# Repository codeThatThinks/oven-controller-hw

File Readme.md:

# MLL Electronics Oven Controller v1.0

A Raspberry Pi Zero-powered PID reflow oven controller -- PCB design files.

## Controller PCBA

## Display PCBA

## License

This project is licensed under the CERN-OHL-W v2. See LICENSE for more details.

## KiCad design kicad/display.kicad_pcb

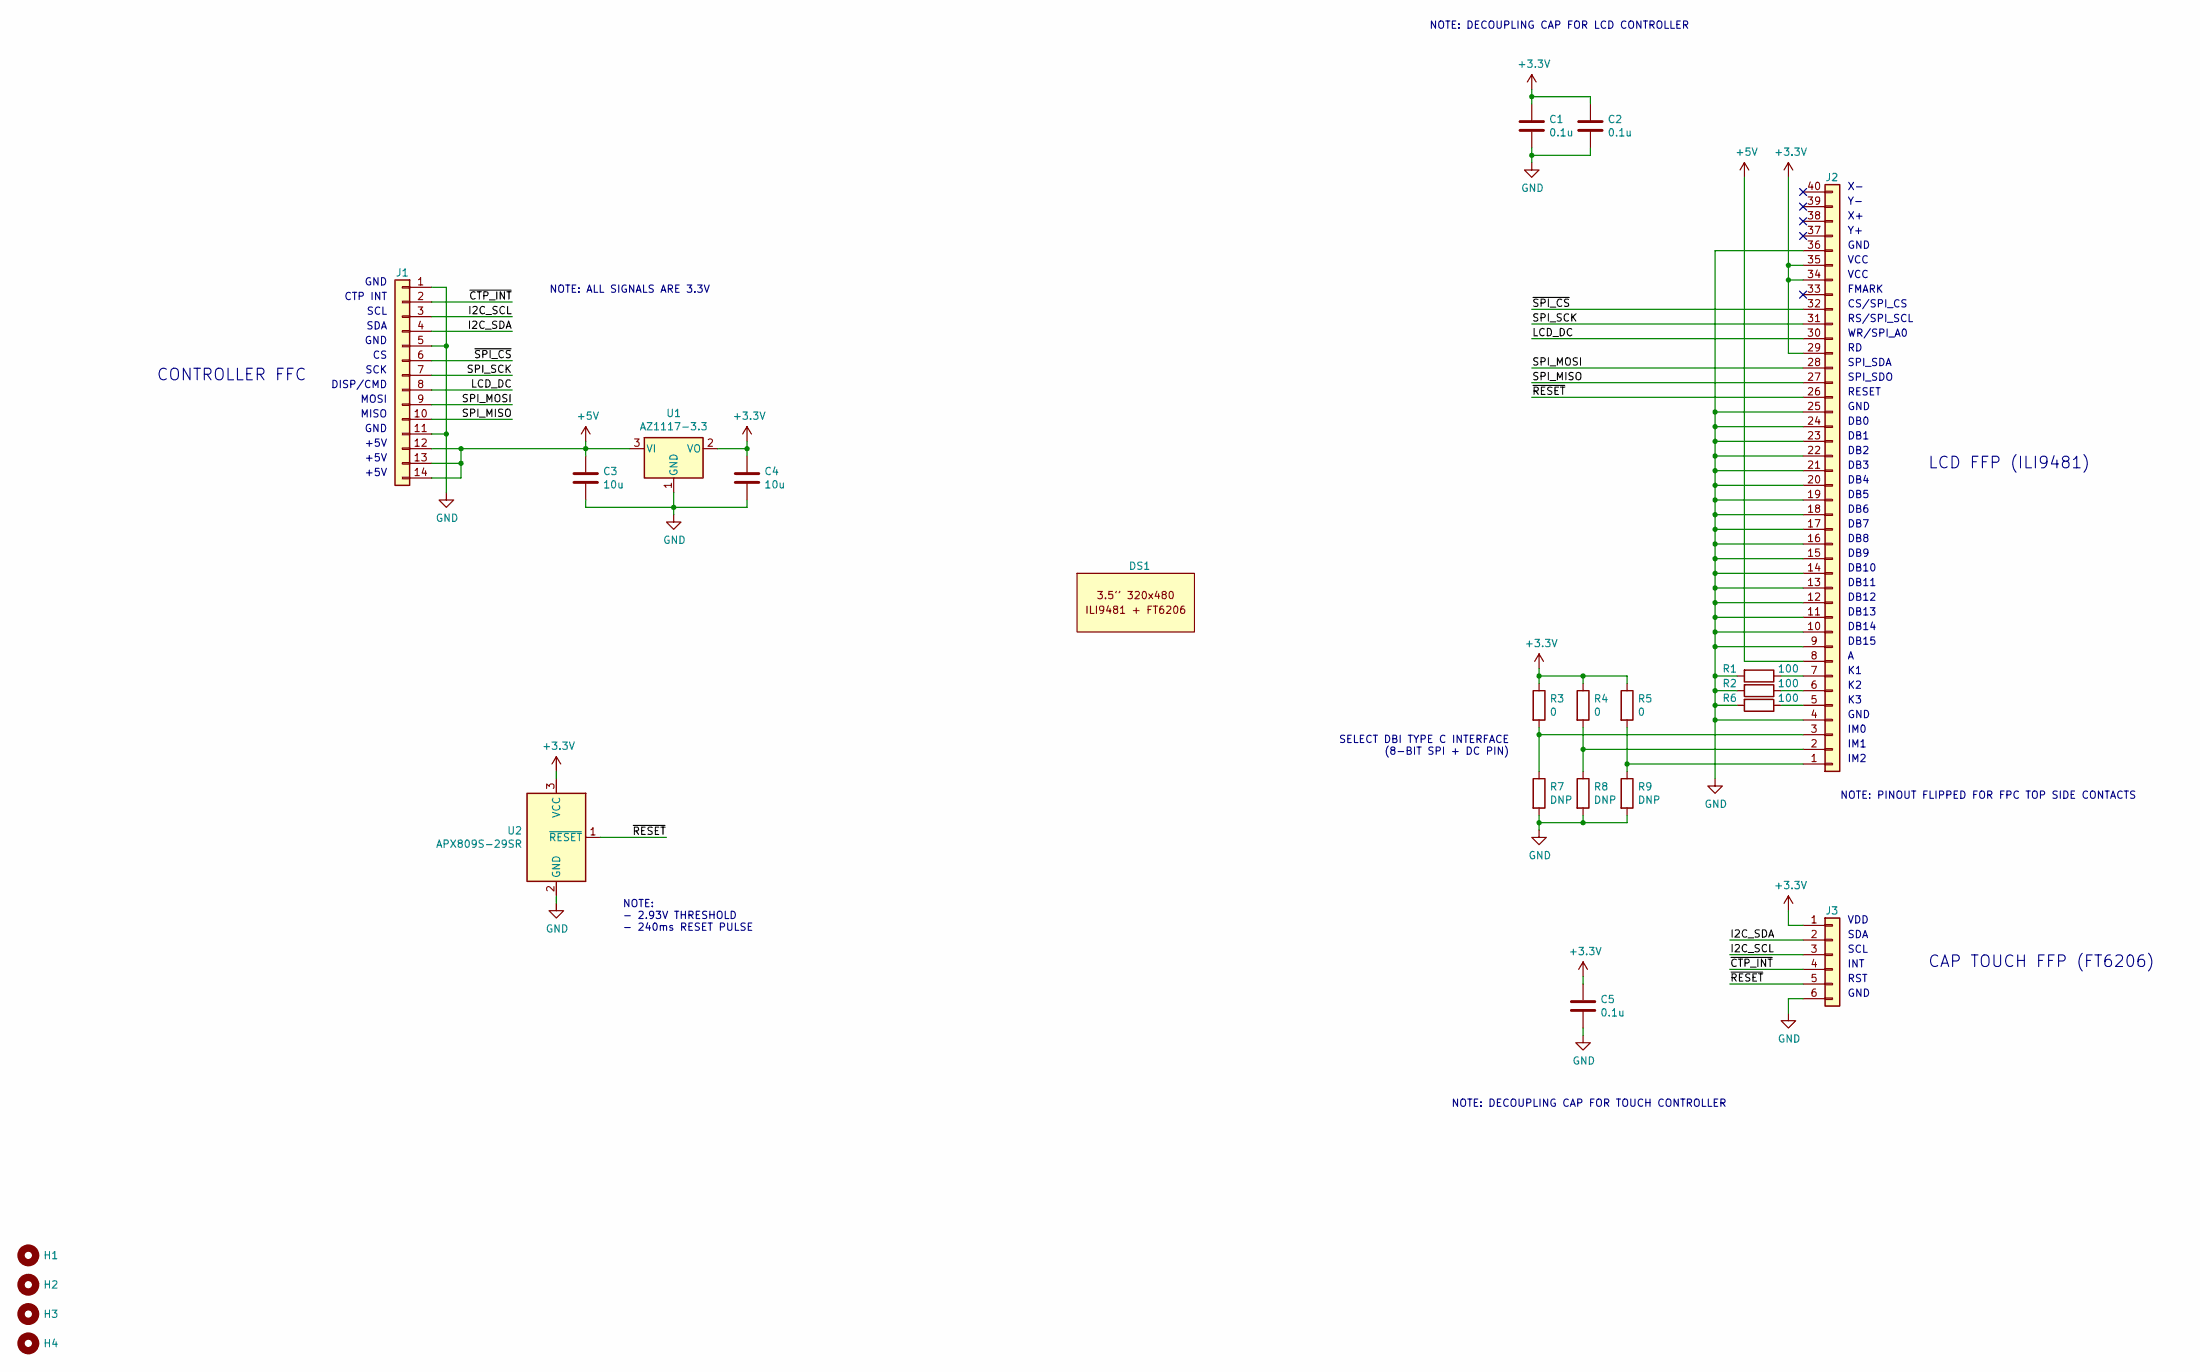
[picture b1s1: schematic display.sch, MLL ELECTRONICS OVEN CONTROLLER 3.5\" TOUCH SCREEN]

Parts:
C1, C2, C5: 0.1u; C_0603_1608Metric
C3, C4: 10u; C_0805_2012Metric
DS1: Display_LiangHaoCai_3.5in_IPS_CTP
H1, H2, H3, H4: MountingHole; MountingHole_3.2mm_M3
J1: CONTROLLER; TE_1-84953-4_1x14_1MP_P1.0_Horizontal
J2: LCD; GCT_FFC2B28-40-G_1x40_1MP_P0.50mm_Horizontal
J3: CTP; GCT_FFC2B28-06-G_1x6_1MP_P0.50mm_Horizontal
R1, R2, R6: 100; R_0603_1608Metric
R3, R4, R5: 0; R_0603_1608Metric
R7, R8, R9: DNP; R_0603_1608Metric
U1: AZ1117-3.3; SOT-223-3_TabPin2
U2: APX809S-29SR; SOT-23

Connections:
+3V3: C1.1, C2.1, C4.1, C5.1, J2.29, J2.34, J2.35, J3.1, R3.1, R4.1, R5.1, U1.2 (VO), U2.3 (VCC)
+5V: C3.1, J1.12, J1.13, J1.14, J2.8, U1.3 (VI)
/I2C_SCL: J1.3, J3.3
/I2C_SDA: J1.4, J3.2
/LCD_DC: J1.8, J2.30
/SPI_MISO: J1.10, J2.27
/SPI_MOSI: J1.9, J2.28
/SPI_SCK: J1.7, J2.31
/~CTP_INT: J1.2, J3.4
/~RESET: J2.26, J3.5, U2.1 (~RESET)
/~SPI_CS: J1.6, J2.32
GND: C1.2, C2.2, C3.2, C4.2, C5.2, J1.1, J1.5, J1.11, J2.4, J2.9, J2.10, J2.11, J2.12, J2.13, J2.14, J2.15, J2.16, J2.17, J2.18, J2.19, J2.20, J2.21, J2.22, J2.23, J2.24, J2.25, J2.36, J3.6, R1.2, R2.2, R6.2, R7.2, R8.2, R9.2, U1.1 (GND), U2.2 (GND)
unnamed: J2.1, R5.2, R9.1
unnamed: J2.2, R4.2, R8.1
unnamed: J2.3, R3.2, R7.1
unnamed: J2.5, R6.1
unnamed: J2.6, R2.1
unnamed: J2.7, R1.1

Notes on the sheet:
GND
VCC
FMARK
CS/SPI_CS
RS/SPI_SCL
WR/SPI_A0
SPI_SDA
SPI_SDO
RESET
DB0
DB1
DB2
DB3
DB4
DB5
DB6
DB7
DB8
DB9
DB10
DB11
DB12
DB13
DB14
DB15
IM0
IM1
IM2
LCD FFP (ILI9481)
CAP TOUCH FFP (FT6206)
VDD
SDA
SCL
INT
RST
NOTE: DECOUPLING CAP FOR LCD CONTROLLER
NOTE: DECOUPLING CAP FOR TOUCH CONTROLLER
NOTE: - 2.93V THRESHOLD - 240ms RESET PULSE
SCK
MOSI

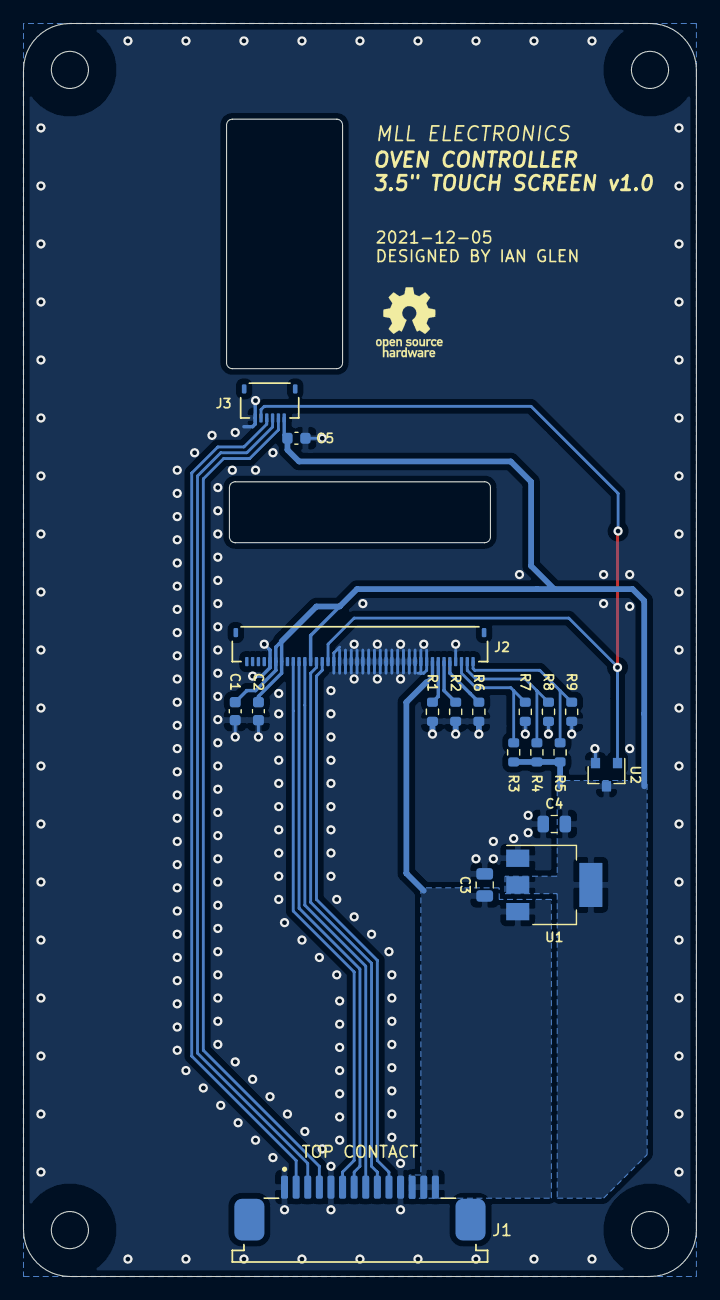
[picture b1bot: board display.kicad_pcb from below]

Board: 2 copper layers, 58.0 x 108.0 mm, 24 parts (19 on the bottom side), 18 nets.

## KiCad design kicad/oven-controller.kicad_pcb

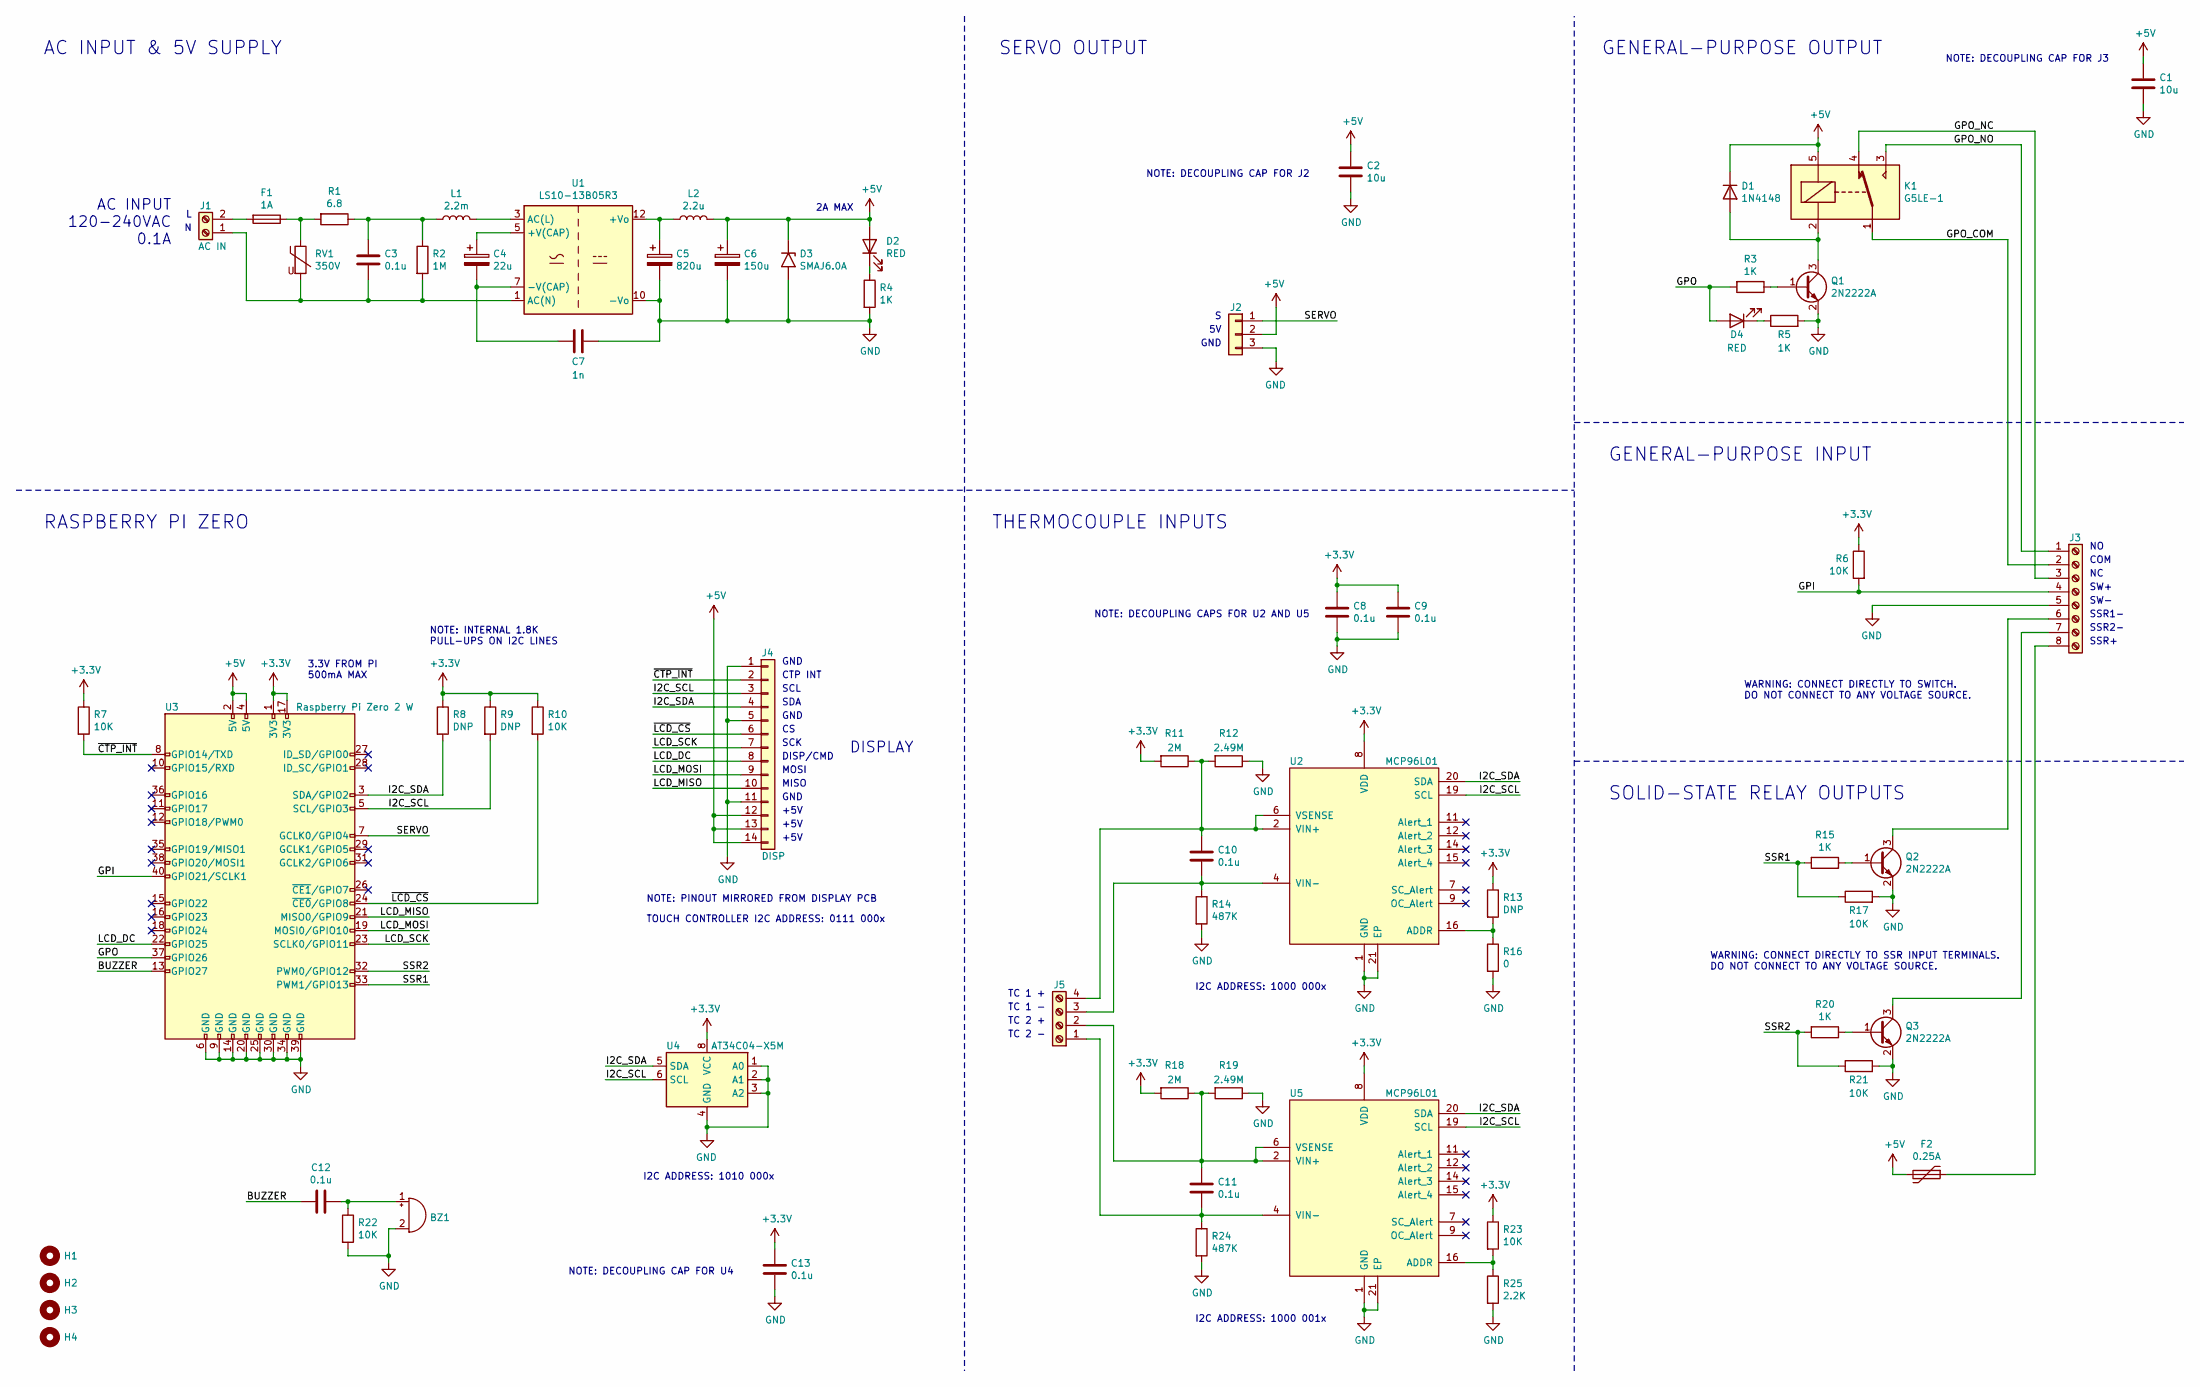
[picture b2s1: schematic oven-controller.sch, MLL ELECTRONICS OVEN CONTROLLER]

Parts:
BZ1: Buzzer; Buzzer_Murata_PKM13EPYH4002-B0
C1, C2: 10u; C_0805_2012Metric
C3: 0.1u; C_Rect_L18.0mm_W5.0mm_P15.00mm_FKS3_FKP3
C4: 22u; CP_Radial_D12.5mm_P5.00mm
C5: 820u; CP_Radial_D10.0mm_P5.00mm
C6: 150u; CP_Radial_D6.3mm_P2.50mm
C7: 1n; C_Disc_D9.0mm_W5.0mm_P12.50mm
C8, C9, C10, C11, C12, C13: 0.1u; C_0603_1608Metric
D1: 1N4148; D_SOD-123
D2, D4: RED; LED_0603_1608Metric
D3: SMAJ6.0A; D_SMA
F1: 1A; Fuseholder_Cylinder-5x20mm_Littelfuse_0PTF0078P
F2: 0.25A; Fuse_1206_3216Metric
H1, H2, H3, H4: MountingHole; MountingHole_3.2mm_M3
J1: AC IN; TerminalBlock_Amphenol_YK-44102_P9.50mm
J2: SERVO; PinHeader_1x03_P2.54mm_Vertical
J3: I/O; TerminalBlock_OST_OSTYK44108030_P9.50mm
J4: DISP; TE_1-1734248-4_1x14_1MP_P1.0_Vertical
J5: THERMOCOUPLE; TerminalBlock_Wuerth_691412320004_P3.81mm
K1: G5LE-1; Relay_SPDT_Omron-G5LE-1
L1: 2.2m; L_Radial_D12.0mm_P6.00mm_MuRATA_1900R
L2: 2.2u; L_Murata_DG8040C
Q1, Q2, Q3: 2N2222A; SOT-23
R1: 6.8; R_Axial_DIN0516_L15.5mm_D5.0mm_P20.32mm_Horizontal
R2: 1M; R_Axial_DIN0207_L6.3mm_D2.5mm_P10.16mm_Horizontal
R3, R4, R5, R15, R20: 1K; R_0603_1608Metric
R6, R7, R10, R17, R21, R22, R23: 10K; R_0603_1608Metric
R8, R9, R13: DNP; R_0603_1608Metric
R11, R18: 2M; R_0603_1608Metric
R12, R19: 2.49M; R_0603_1608Metric
R14, R24: 487K; R_0603_1608Metric
R16: 0; R_0603_1608Metric
R25: 2.2K; R_0603_1608Metric
RV1: 350V; RV_Disc_D15.5mm_W6.1mm_P7.5mm
U1: LS10-13B05R3; Converter_ACDC_CUI_PBO-xxC-x_THT_Vertical
U2, U5: MCP96L01; TQFN-20-1EP_5x5mm_P0.65mm_EP3.25x3.25mm
U3: Raspberry Pi Zero 2 W; Raspberry_Pi_Zero_Socketed_THT_FaceUp_MountingHoles
U4: AT34C04-X5M; TSSOP-8_4.4x3mm_P0.65mm

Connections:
+3V3: C8.1, C9.1, C13.1, R6.1, R7.1, R8.1, R9.1, R10.1, R11.2, R13.1, R18.2, R23.1, U2.8 (VDD), U3.1 (3V3), U3.17 (3V3), U4.8 (VCC), U5.8 (VDD)
+5V: C1.1, C2.1, C6.1, D1.1 (K), D2.2 (A), D3.1 (A1), F2.2, J2.2, J4.12, J4.13, J4.14, K1.5, L2.2, U3.2 (5V), U3.4 (5V)
/BUZZER: C12.2, U3.13 (GPIO27)
/GPI: J3.4, R6.2, U3.40 (GPIO21/SCLK1)
/GPO: D4.2 (A), R3.2, U3.37 (GPIO26)
/GPO_COM: J3.2, K1.1
/GPO_NC: J3.3, K1.4
/GPO_NO: J3.1, K1.3
/I2C_SCL: J4.3, R9.2, U2.19 (SCL), U3.5 (SCL/GPIO3), U4.6 (SCL), U5.19 (SCL)
/I2C_SDA: J4.4, R8.2, U2.20 (SDA), U3.3 (SDA/GPIO2), U4.5 (SDA), U5.20 (SDA)
/LCD_DC: J4.8, U3.22 (GPIO25)
/LCD_MISO: J4.10, U3.21 (MISO0/GPIO9)
/LCD_MOSI: J4.9, U3.19 (MOSI0/GPIO10)
/LCD_SCK: J4.7, U3.23 (SCLK0/GPIO11)
/SERVO: J2.1, U3.7 (GCLK0/GPIO4)
/SSR1: R15.2, R17.1, U3.33 (PWM1/GPIO13)
/SSR2: R20.2, R21.1, U3.32 (PWM0/GPIO12)
/~CTP_INT: J4.2, R7.2, U3.8 (GPIO14/TXD)
/~LCD_CS: J4.6, R10.2, U3.24 (~CE0~/GPIO8)
GND: BZ1.2 (+), C1.2, C2.2, C5.2, C6.2, C7.1, C8.2, C9.2, C13.2, D3.2 (A2), J2.3, J3.5, J4.1, J4.5, J4.11, Q1.2 (E), Q2.2 (E), Q3.2 (E), R4.2, R5.2, R12.1, R14.2, R16.2, R17.2, R19.1, R21.2, R22.2, R24.2, R25.2, U1.10 (-Vo), U2.1 (GND), U2.3 (GND), U2.5 (GND), U2.10 (GND), U2.13 (GND), U2.17 (GND), U2.18 (GND), U2.21 (EP), U3.6 (GND), U3.9 (GND), U3.14 (GND), U3.20 (GND), U3.25 (GND), U3.30 (GND), U3.34 (GND), U3.39 (GND), U4.1 (A0), U4.2 (A1), U4.3 (A2), U4.4 (GND), U5.1 (GND), U5.3 (GND), U5.5 (GND), U5.10 (GND), U5.13 (GND), U5.17 (GND), U5.18 (GND), U5.21 (EP)
unnamed: BZ1.1 (-), C12.1, R22.1
unnamed: C3.1, L1.1, R1.1, R2.1
unnamed: C3.2, J1.1, R2.2, RV1.2, U1.1 (AC(N))
unnamed: C4.1, U1.5 (+V(CAP))
unnamed: C4.2, C7.2, U1.7 (-V(CAP))
unnamed: C5.1, L2.1, U1.12 (+Vo)
unnamed: C10.1, J5.4, R11.1, R12.2, U2.2 (VIN+), U2.6 (VSENSE)
unnamed: C10.2, J5.3, R14.1, U2.4 (VIN-)
unnamed: C11.1, J5.2, R18.1, R19.2, U5.2 (VIN+), U5.6 (VSENSE)
unnamed: C11.2, J5.1, R24.1, U5.4 (VIN-)
unnamed: D1.2 (A), K1.2, Q1.3 (C)
unnamed: D2.1 (K), R4.1
unnamed: D4.1 (K), R5.1
unnamed: F1.1, R1.2, RV1.1
unnamed: F1.2, J1.2
unnamed: F2.1, J3.8
unnamed: J3.6, Q2.3 (C)
unnamed: J3.7, Q3.3 (C)
unnamed: L1.2, U1.3 (AC(L))
unnamed: Q1.1 (B), R3.1
unnamed: Q2.1 (B), R15.1
unnamed: Q3.1 (B), R20.1
unnamed: R13.2, R16.1, U2.16 (ADDR)
unnamed: R23.2, R25.1, U5.16 (ADDR)

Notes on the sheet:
I2C ADDRESS: 1000 000x
NOTE: DECOUPLING CAPS FOR U2 AND U5
THERMOCOUPLE INPUTS
RASPBERRY PI ZERO
AC INPUT & 5V SUPPLY
AC INPUT 120-240VAC 0.1A
2A MAX
3.3V FROM PI 500mA MAX
COM
SOLID-STATE RELAY OUTPUTS
GENERAL-PURPOSE OUTPUT
I2C ADDRESS: 1000 001x
GENERAL-PURPOSE INPUT
WARNING: CONNECT DIRECTLY TO SWITCH. DO NOT CONNECT TO ANY VOLTAGE SOURCE.
I2C ADDRESS: 1010 000x
NOTE: DECOUPLING CAP FOR U4
TOUCH CONTROLLER I2C ADDRESS: 0111 000x
DISPLAY
SCK
MOSI
MISO
DISP/CMD
GND
SCL
SDA
CTP INT
+5V
WARNING: CONNECT DIRECTLY TO SSR INPUT TERMINALS. DO NOT CONNECT TO ANY VOLTAGE SOURCE.
SERVO OUTPUT
SW+
SW-
SSR2-
SSR1-
SSR+
TC 2 -
TC 2 +
TC 1 -
TC 1 +
NOTE: PINOUT MIRRORED FROM DISPLAY PCB
NOTE: DECOUPLING CAP FOR J2

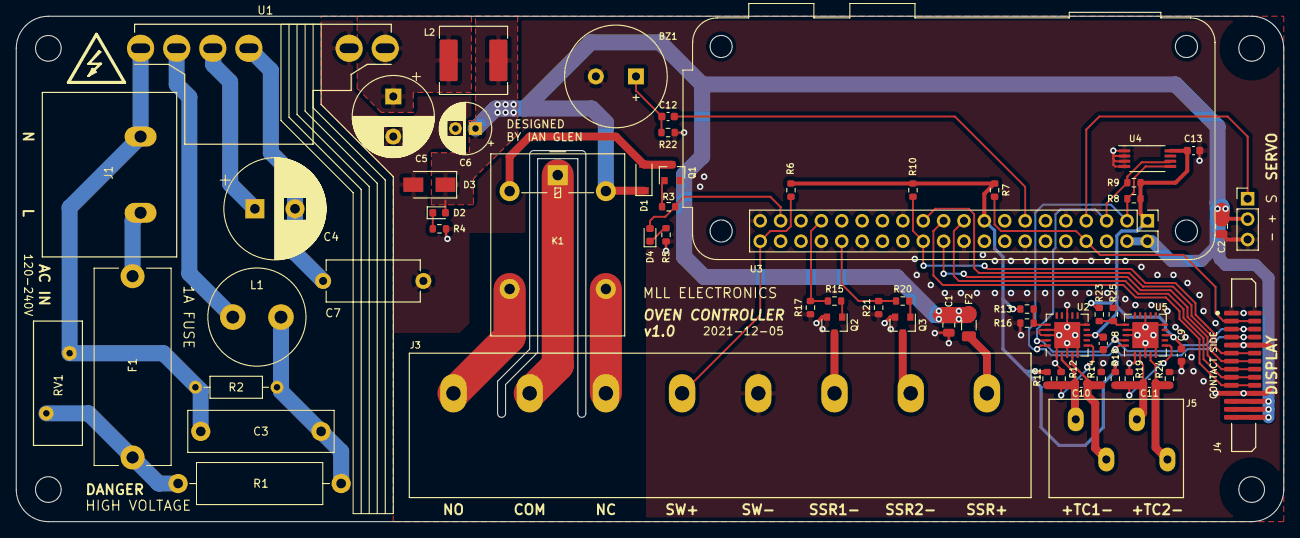
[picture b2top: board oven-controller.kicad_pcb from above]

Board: 2 copper layers, 158.0 x 63.0 mm, 66 parts (0 on the bottom side), 44 nets.

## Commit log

2021-12-09 Initial commit of controller PCBA v1.0
2021-12-09 Fix Readme images
2021-12-11 Initial commit of display PCBA v1.0
2021-12-11 Fix PCB images

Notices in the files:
kicad/display.kicad_pcb:
LICENSED UNDER CERN-OHL-W V2
